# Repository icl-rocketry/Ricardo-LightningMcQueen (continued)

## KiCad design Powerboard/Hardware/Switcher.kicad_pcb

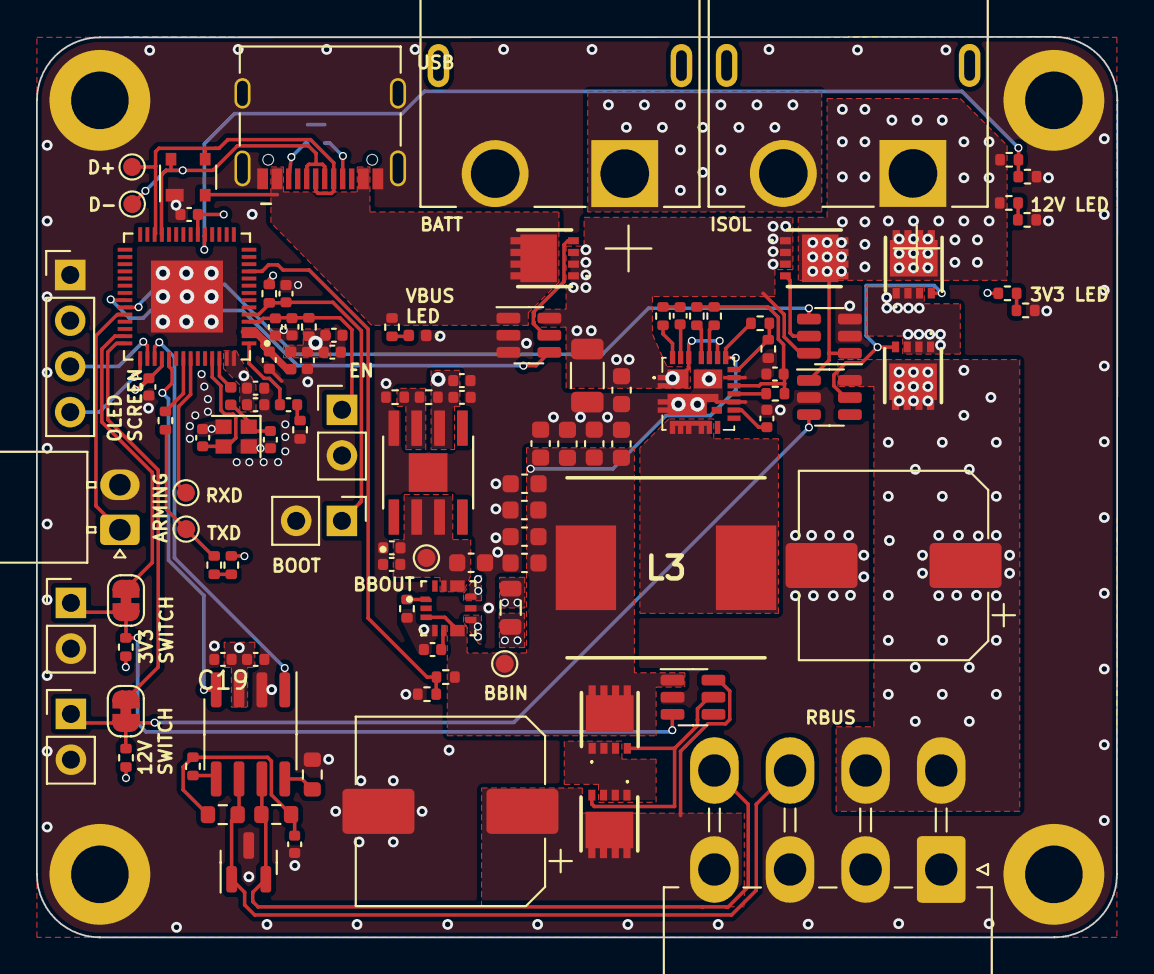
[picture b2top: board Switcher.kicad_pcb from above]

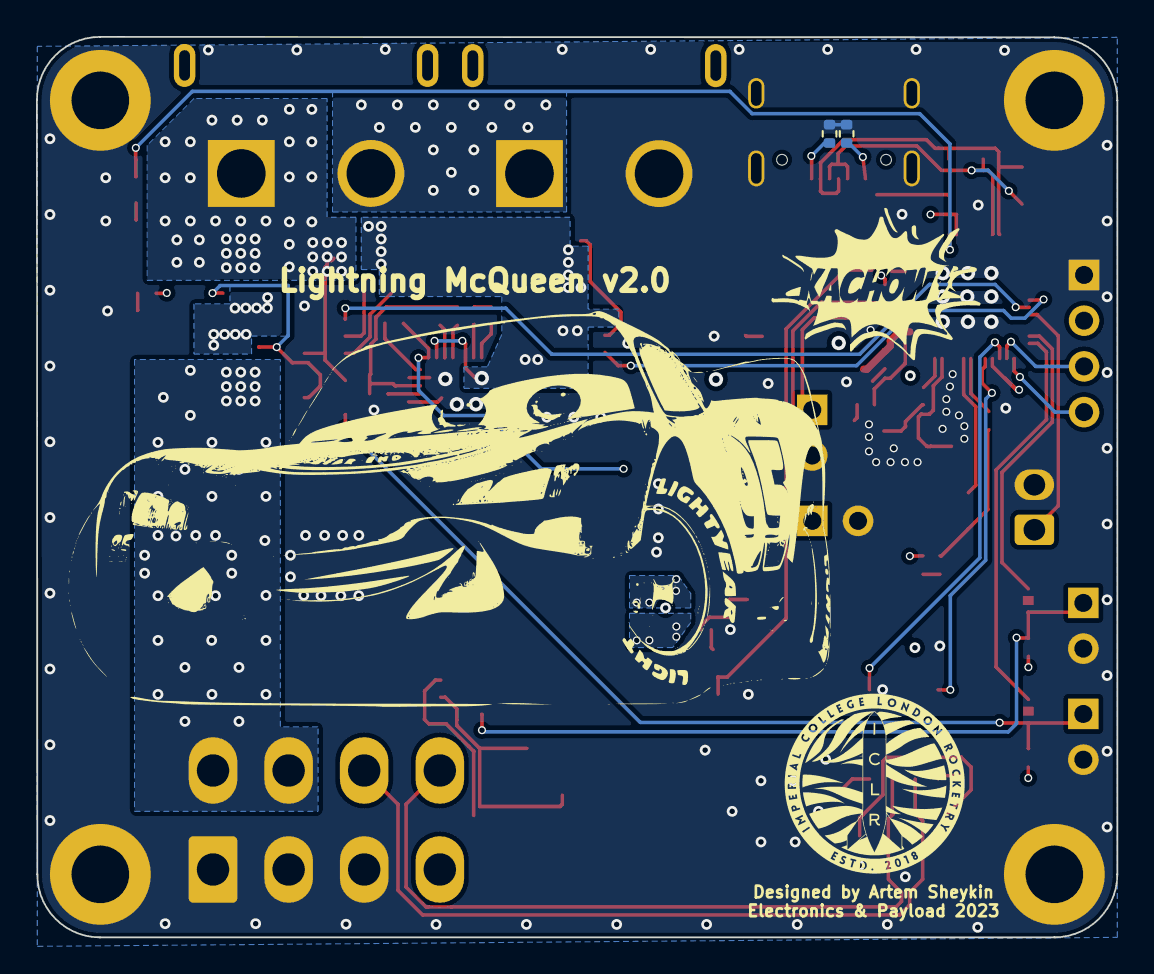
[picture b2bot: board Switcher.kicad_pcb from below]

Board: 4 copper layers, 60.0 x 50.0 mm, 116 parts (3 on the bottom side), 68 nets.

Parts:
3V3LED1: 3V3LED; R_0402_1005Metric
12VLED1: 12V_LED; R_0402_1005Metric
BOOTJUMPER1: Conn_01x02_Male; PinHeader_1x02_P2.54mm_Vertical
C1, C19, C51, C53: 10uF; C_0402_1005Metric
C2, C4, C7, C46, C49: 1uF; C_0402_1005Metric
C3, C5, C6, C8, C10, C11, C42, C54: 0.1uF; C_0402_1005Metric
C9: 10nF; C_0402_1005Metric
C12: DNP; C_0402_1005Metric
C13, C14: C; C_0402_1005Metric
C15, C25, C30, C32, C34, C36, C38, C50: 22uF; C_0603_1608Metric
C17: 10uF; C_0603_1608Metric
C18: 100nF; C_0402_1005Metric
C20: 47nF; C_0402_1005Metric
C23: 1000uF; CP_Elec_10x10
C24: 180uF; CP_Elec_10x10
C40: 47uF; C_1206_3216Metric
C44: 100nF; C_0603_1608Metric
C47, C52: 4.7uF; C_0402_1005Metric
D1: SP0503BAHT; SOT-143
D2: SM712_SOT23; SOT-23
ENJUMPER1: Conn_01x02_Male; PinHeader_1x02_P2.54mm_Vertical
H1, H2, H3, H4: MountingHole_Pad; MountingHole_3.2mm_M3_DIN965_Pad
IC2: SiC437BED-T1-GE3; SiC437BEDT1GE3
J1: Conn_01x03_MountingPin; Molex_Nano-Fit_105313-xx02_1x02_P2.50mm_Horizontal
J3: USB_C_Receptacle_USB2.0; USB_C_Receptacle_Palconn_UTC16-G
J4, J6: Conn_01x02_Male; PinHeader_1x02_P2.54mm_Vertical
J5: Conn_01x08_Male; Molex_Mini-Fit_Jr_5569-08A2_2x04_P4.20mm_Horizontal
J7, J9: XT60PW-M; AMASS_XT60PW-M
J8: Conn_01x04_Male; PinHeader_1x04_P2.54mm_Vertical
JP2, JP3: SolderJumper_2_Bridged; SolderJumper-2_P1.3mm_Bridged_RoundedPad1.0x1.5mm
L1: 2.0nH; L_0402_1005Metric
L2: 20nH; L_0402_1005Metric
L3: SRP1050WA-3R3M; INDPM110100X540N
L5: 1uH; L_0805_2012Metric
Q1, Q2, Q3, Q4, Q5, Q6: PXP012-30QLJ; PXP01230QLJ
R1: 14k; R_0402_1005Metric
R2: 56k; R_0402_1005Metric
R3, R6: 10K; R_0402_1005Metric
R4: 499; R_0402_1005Metric
R5, R7, R12: 470; R_0402_1005Metric
R8: DNP; R_0402_1005Metric
R9: 3k; R_0402_1005Metric
R10, R11: 5.1k; R_0402_1005Metric
R13, R18, R19, R21, R22, R24, R25: 10k; R_0402_1005Metric
R14: 47k; R_0402_1005Metric
R15: 0; R_0603_1608Metric
R16, R17: 60; R_0603_1608Metric
R20: 45k; R_0402_1005Metric
R23: 0; R_0402_1005Metric
R26: 160k; R_0402_1005Metric
R29: 51k; R_0402_1005Metric
R30: 2.2; R_0402_1005Metric
R31: 200k; R_0402_1005Metric
TP1: locked; TestPoint_Pad_D1.0mm
TP2, TP3, TP4, TP5, TP6: TestPoint; TestPoint_Pad_D1.0mm
TXLED1: TX_LED; R_0402_1005Metric
U1, U6, U7, U8: LTC4412xS6; TSOT-23-6
U2: ESP32-S3; QFN40P700X700X90-57N
U4: MAX77827AEFD+T; CONV_MAX77827AEFD+T
U5: SN65HVD230; SOIC-8_3.9x4.9mm_P1.27mm
U10: SC4215; SOIC127P599X175-9N
USBLED1: USB_LED; LED_0402_1005Metric
Y1: 40MHz±10ppm; Crystal_SMD_2016-4Pin_2.0x1.6mm
locked: LOGO; LMQ

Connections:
+3V3: C1.1, C4.1, C5.1, C7.1, C9.1, C10.1, C11.1, C18.1, C19.1, C53.2, C54.2, J8.2, L1.1, R2.1, R3.1, R5.1, R6.1, R7.2, R18.1, R19.1, U2.20 (VDD3P3_RTC), U2.46 (VDD3P3_CPU), U2.55 (VDDA), U2.56 (VDDA), U5.3 (VCC), U10.6 (VOUT)
+12V: J9.1 (+), Q4.5 (D_1), Q4.6 (D_2), Q4.7 (D_3), Q4.8 (D_4), Q4.9 (D_5), Q5.5 (D_1), Q5.6 (D_2), Q5.7 (D_3), Q5.8 (D_4), Q5.9 (D_5), R9.1, R14.1, U1.1 (VIN), U7.1 (VIN)
/3V3Filter/BBOUT: C50.1, C51.1, C52.1, TP6.1, U4.11 (OUT), U4.13 (OUTS), U10.2 (EN), U10.3 (VIN)
/3V3Filter/BIAS: C49.1, U4.5 (BIAS)
/3V3Filter/FBIn: R2.2, R13.1, U10.7 (ADJ)
/3V3Filter/LX1: L5.1, U4.8 (LX1)
/3V3Filter/LX2: L5.2, U4.10 (LX2)
/3V3Filter/SEL: R1.1, U4.1 (SEL)
/3V3LOG: R24.2, R26.1, U2.11 (GPIO6/ADC1_CH5)
/3V3_SWITCH: JP2.2 (B), U2.41 (GPIO36)
/12V_SWITCH: JP3.2 (B), U2.42 (GPIO37)
/BOOT: BOOTJUMPER1.1, C8.1, R6.2, U2.5 (GPIO0/BOOT)
/Bucks/BOOT: C42.1, IC2.23 (BOOT)
/Bucks/FB: IC2.17 (FB), R20.1, R21.1
/Bucks/MODE_1: IC2.21 (_MODE_1), R29.2
/Bucks/MODE_2: IC2.20 (MODE_2), R31.1
/Bucks/PHASE: IC2.24 (PHASE), R30.1
/Bucks/SW: IC2.5 (SW_1), IC2.6 (SW_2), IC2.7 (SW_3), IC2.8 (SW_4), IC2.9 (SW_5), IC2.30 (SW_6), L3.2
/Bucks/Vdd: C46.2, IC2.15 (VDD), R25.1, R29.1, R31.2
/CAN+: D2.2 (A2), J5.8, R16.1, U5.7 (CANH)
/CAN-: D2.1 (A1), J5.7, R17.2, U5.6 (CANL)
/CAN/Vref: R23.1, U5.5 (Vref)
/CAN_RX: U2.47 (MTDI/JTAG/GPIO41), U5.4 (R)
/CAN_TX: U2.45 (MTDO/JTAG/GPIO40), U5.1 (D)
/CHIP_PU: C2.1, C3.1, ENJUMPER1.1, R3.2, U2.4 (CHIP_PU/RESET)
/Data+: D1.3 (K), J3.A7 (D-), J3.B7 (D-), TP1.1, U2.26 (GPIO20/USB_D+/ADC2_CH9)
/Data-: D1.4 (K), J3.A6 (D+), J3.B6 (D+), TP2.1, U2.25 (GPIO19/USB_D-/ADC2_CH8)
/DeploymentVoltage: R14.2, R22.1, U2.19 (GPIO14/ADC2_CH3)
/LIPOPOWER: U1.4 (STAT), U2.37 (SPICLK_P/GPIO47)
/PDU_EN: J1.1, U2.38 (GPIO33)
/SCL: J8.3, U2.44 (MTCK/JTAG/GPIO39)
/SDA: J8.4, U2.43 (GPIO38)
/TXD: R4.1, TP4.1, TXLED1.1 (K)
/USBPOWER: U2.36 (SPICLK_N/GPIO48), U8.4 (STAT)
GND: 3V3LED1.1 (K), 12VLED1.1 (K), BOOTJUMPER1.2, C1.2, C2.2, C3.2, C4.2, C5.2, C6.2, C7.2, C8.2, C9.2, C10.2, C11.2, C13.2, C14.2, C15.1, C17.2, C18.2, C19.2, C20.2, C23.2, C24.2, C25.1, C30.1, C32.1, C34.1, C36.1, C38.1, C40.2, C44.2, C46.1, C47.2, C49.2, C50.2, C51.2, C52.2, C53.1, C54.1, D1.1 (A), D2.3 (common), ENJUMPER1.2, H1.1, H2.1, H3.1, H4.1, IC2.3 (P_GND_1), IC2.4 (P_GND_2), IC2.13 (P_GND_3), IC2.16 (A_GND), IC2.25 (AGND), IC2.27 (PGND), IC2.29 (P_GND_4), J1.2, J3.A1 (GND), J3.A12 (GND), J3.B1 (GND), J3.B12 (GND), J3.S1 (SHIELD), J4.2, J5.1, J5.2, J5.3, J6.2, J7.2 (-), J8.1, R1.2, R8.1, R10.2, R11.1, R13.2, R15.2, R21.2, R22.2, R26.2, U1.2 (GND), U1.3 (CTL), U2.57 (GND), U4.4 (AGND), U4.9 (PGND), U5.2 (GND), U6.2 (GND), U7.2 (GND), U8.2 (GND), U8.3 (CTL), U10.8 (GND), U10.9 (GND), USBLED1.1 (K), Y1.2, Y1.4
unnamed: 3V3LED1.2 (A), R7.1
unnamed: 12VLED1.2 (A), R9.2
unnamed: C6.1, L1.2, U2.2 (VDD3P3), U2.3 (VDD3P3)
unnamed: C12.1, R8.2
unnamed: C14.1, L2.2, Y1.1
unnamed: C20.1, R16.2, R17.1, R23.2
unnamed: C42.2, R30.2
unnamed: C40.1, C44.1, IC2.1 (V_IN_1), IC2.2 (V_IN_2), IC2.19 (EN), IC2.22 (VIN_1), IC2.26 (VIN_2), Q5.1 (S_1), Q5.2 (S_2), Q5.3 (S_3), Q6.1 (S_1), Q6.2 (S_2), Q6.3 (S_3), U1.6 (SENSE), U8.6 (SENSE)
unnamed: IC2.14 (P_GOOD), R25.2
unnamed: C47.1, IC2.12 (V_DRV)
unnamed: J3.A5 (CC1), R10.1
unnamed: J3.B5 (CC2), R11.2
unnamed: J4.1, JP2.1 (A), R18.2, U6.3 (CTL)
unnamed: C23.1, J5.4, Q1.5 (D_1), Q1.6 (D_2), Q1.7 (D_3), Q1.8 (D_4), Q1.9 (D_5), U6.6 (SENSE)
unnamed: C24.1, J5.5, J5.6, Q3.5 (D_1), Q3.6 (D_2), Q3.7 (D_3), Q3.8 (D_4), Q3.9 (D_5), U7.6 (SENSE)
unnamed: J6.1, JP3.1 (A), R19.2, U7.3 (CTL)
unnamed: J7.1 (+), J9.2 (-)
unnamed: Q1.4 (G), Q2.4 (G), U6.5 (GATE)
unnamed: Q1.1 (S_1), Q1.2 (S_2), Q1.3 (S_3), Q2.1 (S_1), Q2.2 (S_2), Q2.3 (S_3)
unnamed: Q3.4 (G), Q4.4 (G), U7.5 (GATE)
unnamed: Q3.1 (S_1), Q3.2 (S_2), Q3.3 (S_3), Q4.1 (S_1), Q4.2 (S_2), Q4.3 (S_3)
unnamed: Q5.4 (G), U1.5 (GATE)
unnamed: Q6.4 (G), U8.5 (GATE)
unnamed: R5.2, TXLED1.2 (A)
unnamed: C12.2, U2.1 (LNA_IN/RF)
unnamed: TP5.1, U2.50 (U0RXD/PROG/GPIO44)
unnamed: R4.2, U2.49 (U0TXD/PROG/GPIO43)
unnamed: C13.1, U2.53 (XTAL_N), Y1.3
unnamed: L2.1, U2.54 (XTAL_P)
unnamed: R15.1, U5.8 (Rs)
unnamed: R12.2, USBLED1.2 (A)
RBUS_uC_V: C15.2, C17.1, C25.2, C30.2, C32.2, C34.2, C36.2, C38.2, IC2.18 (V_OUT), L3.1, Q2.5 (D_1), Q2.6 (D_2), Q2.7 (D_3), Q2.8 (D_4), Q2.9 (D_5), R20.2, R24.1, TP3.1, U4.3 (EN), U4.6 (IN), U6.1 (VIN)
VBUS: D1.2 (K), J3.A4 (VBUS), J3.A9 (VBUS), J3.B4 (VBUS), J3.B9 (VBUS), Q6.5 (D_1), Q6.6 (D_2), Q6.7 (D_3), Q6.8 (D_4), Q6.9 (D_5), R12.1, U8.1 (VIN)

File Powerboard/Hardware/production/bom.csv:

Designator,Footprint,Quantity,Value,LCSC Part #
3V3LED1,0402,1,CYAN_LED,
"BATTLED1, CANRXLED1",0402,2,ORANGE_LED,
"BOOTJUMPER1, ENJUMPER1, J4, J6",PinHeader_1x02_P2.54mm_Vertical,4,Conn_01x02_Male,
"C1, C19, C51, C53",0402,4,10uF,
"C10, C11, C3, C42, C5, C54, C6, C8",0402,8,0.1uF,
"C12, R8",0402,2,DNP,
"C13, C14",0402,2,11pF,
"C15, C25, C30, C32, C34, C36, C38, C50",0603,8,22uF,
C17,0603,1,10uF,
C18,0402,1,100nF,
"C2, C4, C46, C49, C7",0402,5,1uF,
C20,0402,1,47nF,
C23,CP_Elec_10x10,1,1000uF,
C24,CP_Elec_10x10,1,180uF,
C40,1206,1,47uF,
C44,0603,1,100nF,
"C47, C52",0402,2,4.7uF,
C9,0402,1,10nF,
CANTXLED1,0402,1,EMERALD_LED,
D1,SOT-143,1,SP0503BAHT,
D2,SOT-23,1,SM712_SOT23,
DEPLED1,0402,1,RED_LED,
"H1, H2, H3, H4",MountingHole_3.2mm_M3_DIN965_Pad,4,MountingHole_Pad,
IC2,SiC437BEDT1GE3,1,SiC437AED-T1-GE3,
J1,Molex_Nano-Fit_105313-xx02_1x02_P2.50mm_Horizontal,1,Conn_01x03_MountingPin,
J2,PinHeader_1x02_P2.54mm_Vertical,1,FAN,
J3,USB_C_Receptacle_Palconn_UTC16-G,1,USB_C_Receptacle_USB2.0,
J5,Molex_Mini-Fit_Jr_5569-08A2_2x04_P4.20mm_Horizontal,1,Conn_01x08_Male,
"J7, J9",AMASS_XT60PW-M,2,XT60PW-M,
J8,PinHeader_1x04_P2.54mm_Vertical,1,Conn_01x04_Male,
"JP1, JP2",SolderJumper-2_P1.3mm_Bridged_RoundedPad1.0x1.5mm,2,SolderJumper_2_Bridged,
L1,0402,1,2.0nH,
L2,0402,1,20nH,
L3,INDPM110100X540N,1,SRP1050WA-3R3M,
L5,0805,1,1uH,
LOGICLED1,0402,1,BLUE_LED,
Q1,SOT-723,1,"SSM3K15AMFV,L3F",
"Q10, Q7, Q8, Q9",SQS850ENT1_GE3,4,SQS141ELNW-T1_GE3,
"Q5, Q6",PXP01230QLJ,2,PXP012-30QLJ,
R1,0402,1,14k,
"R10, R11, R12",0402,3,5.1k,
"R13, R18, R21, R22, R24, R25, R3, R32, R35, R6",0402,10,10k,
"R14, R28",0402,2,47k,
R15,0603,1,0,
"R16, R17",0603,2,60,
"R19, R34, R36",0402,3,1k,
R2,0402,1,56k,
R20,0402,1,45k,
R23,0402,1,0,
R26,0402,1,160k,
"R27, R9",0402,2,3k,
R29,0402,1,51k,
R30,0402,1,2.2,
R31,0402,1,100k,
"R33, R5, R7",0402,3,470,
R4,0402,1,499,
"TP1, TP2, TP3, TP4, TP5, TP6",TestPoint_Pad_D1.0mm,6,TestPoint,
TXLED1,0402,1,GREEN_LED,
"U1, U6, U7, U8",TSOT-23-6,4,LTC4412xS6,
U10,SOIC127P599X175-9N,1,SC4215,
U2,QFN40P700X700X90-57N,1,ESP32-S3,
U4,CONV_MAX77827AEFD+T,1,MAX77827AEFD+T,
U5,SOIC-8_3.9x4.9mm_P1.27mm,1,SN65HVD230,
USBLED1,0402,1,WHITE_LED,
Y1,Crystal_SMD_2016-4Pin_2.0x1.6mm,1,40MHz±10ppm,

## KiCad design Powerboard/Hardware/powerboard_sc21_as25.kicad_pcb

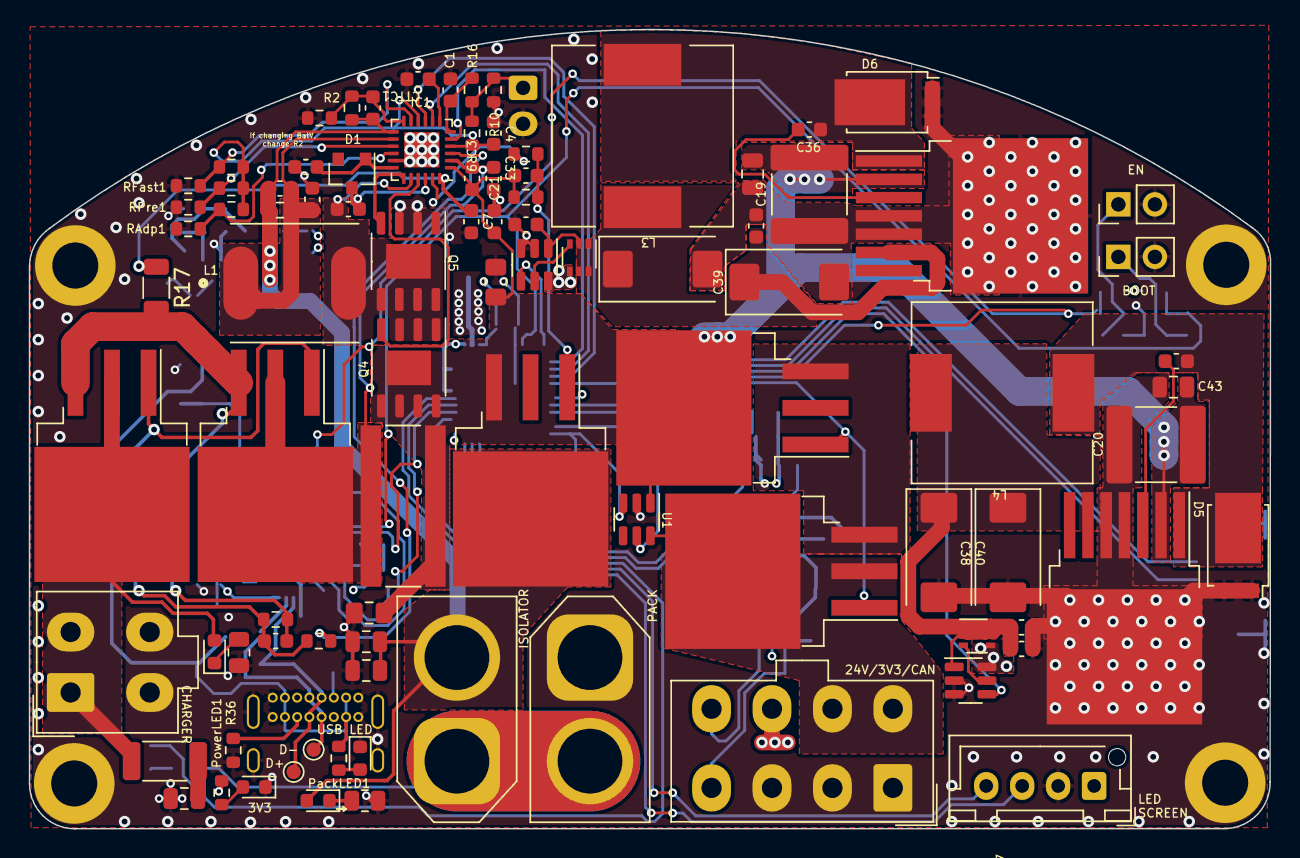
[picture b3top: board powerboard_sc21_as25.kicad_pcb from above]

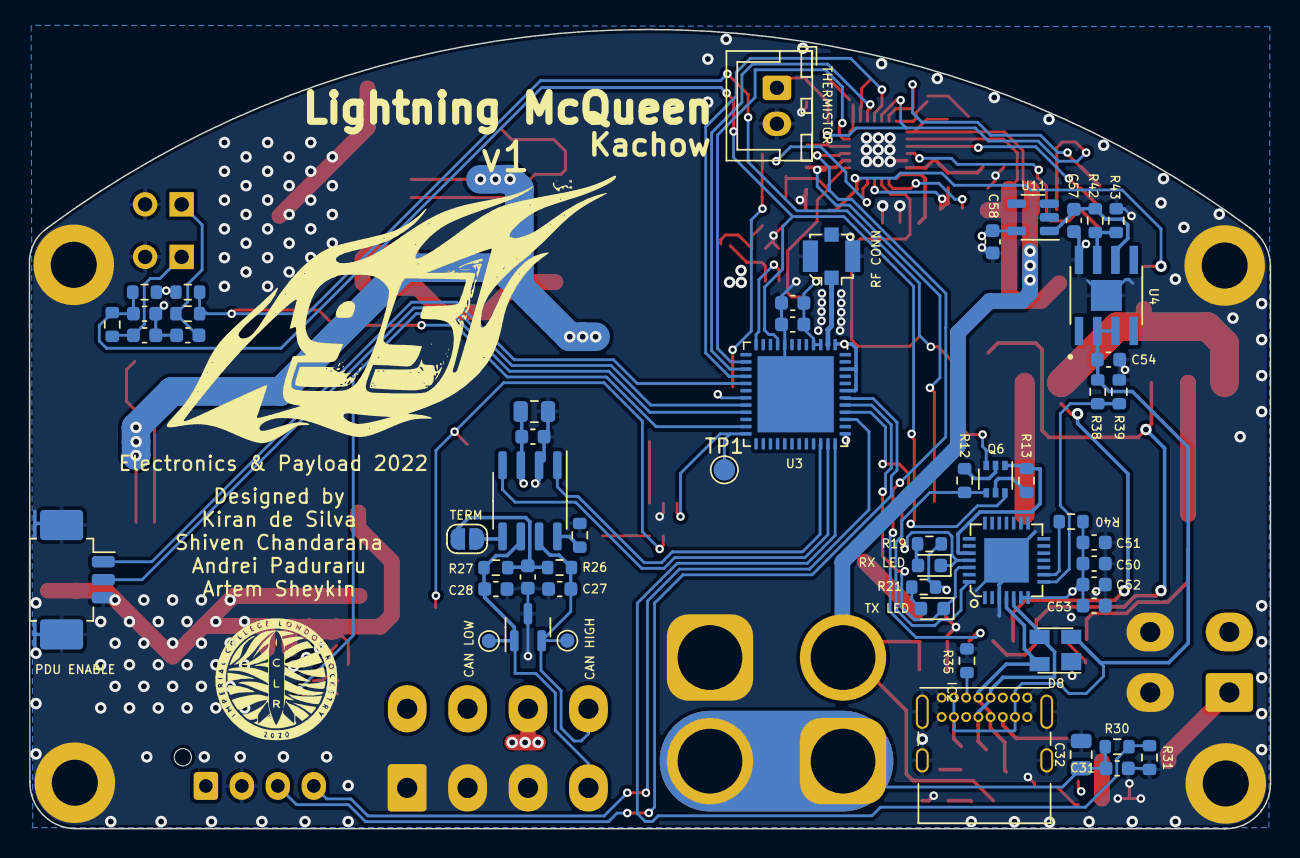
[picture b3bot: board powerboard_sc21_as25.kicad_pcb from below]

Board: 4 copper layers, 86.3 x 55.6 mm, 151 parts (56 on the bottom side), 83 nets.

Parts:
C1, C3, C6, C10, C11, C14, C15, C21, C24, C26, C31, C33, C48, C49, C51, C53: 0.1uF; C_0603_1608Metric
C2, C4, C5, C7, C17, C18: 1uF; C_0603_1608Metric
C8, C9: 10uF; C_0805_2012Metric_Pad1.18x1.45mm_HandSolder
C12, C13, C25, C32: 10uF; C_0805_2012Metric
C16: 2.2uF; C_0805_2012Metric
C19, C20: 47uF; C_2220_5650Metric
C22, C54, C57: 10uF; C_0603_1608Metric
C23: 100nF; C_0603_1608Metric
C27: 220pF; C_0603_1608Metric
C28: 220 pF; C_0603_1608Metric
C36, C37: 0.01uF; C_0603_1608Metric
C38, C39, C40, C41: 330uF; CP_EIA-7343-30_AVX-N
C42, C43: 0.47uF; C_0805_2012Metric
C44, C45: 22uF; C_0603_1608Metric
C50: 1.0uF; C_0603_1608Metric
C52, C58: 4.7uF; C_0603_1608Metric
CTTC1: 22nF; C_0603_1608Metric
Cff1: 22pF; C_0603_1608Metric
D1: BAT54; D_SOT-23_ANK
D2, D3, D7, D9: LED; LED_0603_1608Metric
D4: SM712_SOT23; SOT-23
D5, D6: DST1550S; TO-277B
D8: SP0503BAHT; SOT-143
H1, H2, H3, H4: MountingHole_Pad; MountingHole_3.2mm_M3_DIN965_Pad
IC1: BQ24618RGET-iclr; VQFN-24-1EP_4x4mm_P0.5mm_EP2.45x2.45mm
IC2: CP2102; QFN28G_0.5-5X5MM
J1: Thermistor Connection 103AT NTC; JST_XH_B2B-XH-A_1x02_P2.50mm_Vertical
J2, J3: Conn_01x02_Male; PinHeader_1x02_P2.54mm_Vertical
J4: Conn_01x08_Male; Molex_Mini-Fit_Jr_5566-08A_2x04_P4.20mm_Vertical
J5: Conn_01x04_Male; Molex_Mini-Fit_Jr_5566-04A_2x02_P4.20mm_Vertical
J6: Conn_01x02_Male; AMASS_XT60-M_1x02_P7.20mm_Vertical
J7: IsolationSwitch; AMASS_XT60-M_1x02_P7.20mm_Vertical
J8: USB_C_Receptacle_USB2.0; USB_C_Receptacle_GCT_USB4085
J9: Conn_Coaxial; U.FL_Molex_MCRF_73412-0110_Vertical
J10: Conn_01x04_Male; JST_XH_B4B-XH-AM_1x04_P2.50mm_Vertical
J11: Conn_01x03_MountingPin; Molex_PicoBlade_53261-0371_1x03-1MP_P1.25mm_Horizontal
JP1: SolderJumper_2_Open; SolderJumper-2_P1.3mm_Open_RoundedPad1.0x1.5mm
L1: 6.8uH; INDM8681X400N
L3, L4: 15uH; L_12x12mm_H8mm
PackLED1: LED; LED_0603_1608Metric
PowerLED1: LED; LED_0603_1608Metric
Q1, Q2, Q3, Q7, Q8: RSJ250P10TL; TO-263-3_TabPin2
Q4, Q5: RS1G120MN; HSOP-8-1EP_3.9x4.9mm_P1.27mm_EP2.41x3.1mm
Q6: MMDT2222A; SOT-363_SC-70-6
Q9, Q10: MCH6351; SOT-363_SC-70-6
R1, R4, R11, R12, R13, R24, R31, R43: 10k; R_0603_1608Metric
R2: 110k; R_0603_1608Metric
R3, R5, R7, R14, R15: 100k; R_0603_1608Metric
R6, R8, R19, R21, R22, R37: 470; R_0603_1608Metric
R9: 2.7k; R_0603_1608Metric
R10: 10.5k; R_0603_1608Metric
R16: 100; R_0603_1608Metric
R17: 10; R_1206_3216Metric
R18, R32: 1k; R_0603_1608Metric
R20: 2; R_2010_5025Metric
R26, R27: 60; R_0603_1608Metric
R28, R29: 3k; R_0805_2012Metric
R30: 75k; R_0603_1608Metric
R35, R36: 5.1k; R_0603_1608Metric
R38: 24k; R_0603_1608Metric
R39: 47k; R_0603_1608Metric
R40: 4.7k; R_0603_1608Metric
R42: 56k; R_0603_1608Metric
RAC1: FCSL110R010FER; RESC50110X70N
RAdp1: 150k; R_0603_1608Metric
RFast1: 32k; R_0603_1608Metric
RPre1: 13k; R_0603_1608Metric
RSR1: 10m; R_0603_1608Metric
TP1: TestPoint; TestPoint_Pad_D1.5mm
TP14, TP15, TP23, TP24: TestPoint; TestPoint_Pad_D1.0mm
U1, U8, U9: LTC4412xS6; TSOT-23-6
U2: SN65HVD230; SOIC-8_3.9x4.9mm_P1.27mm
U3: ESP32-PICO-D4; QFN-48-1EP_7x7mm_P0.5mm_EP5.3x5.3mm
U4: SC4216H; SOIC127P599X175-9N
U6, U7: LM2679T-3.3-iclr; TO-263-7_TabPin4
U11: LTC4411; SOT-23-5

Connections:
+3V3: C22.1, C23.1, C24.1, C25.1, C50.1, C51.1, C52.2, C53.2, C58.1, IC2.6 (VDD), IC2.7 (REGIN), J4.7, J10.1, Q9.4 (S), Q10.4 (S), R4.1, R11.1, R19.2, R21.2, R22.2, R40.1, U2.3 (VCC), U3.1 (VDDA), U3.3 (VDDA3P3), U3.4 (VDDA3P3), U3.19 (VDD3P3_RTC), U3.37 (VDD3P3_CPU), U3.43 (VDDA), U3.46 (VDDA), U8.6 (SENSE), U9.6 (SENSE), U11.5 (OUT)
+24V: C3.2, C8.1, C9.1, C15.1, C19.1, C20.1, C21.1, C42.1, C43.1, IC1.1 (ACN), Q3.3, Q4.5 (D), Q4.6 (D), Q4.7 (D), Q4.8 (D), Q4.9 (D), Q8.2, R15.2, RAC1.2, U1.1 (VIN), U6.2 (VIN), U7.2 (VIN)
/3.3STAT1: U3.12 (IO32), U9.4 (STAT)
/3.3STAT2: U3.21 (IO15), U8.4 (STAT)
/BATTSTAT1: IC1.5 (STAT1), U3.14 (IO25)
/BATTSTAT2: IC1.9 (STAT2), U3.16 (IO27)
/BOOT: Q6.3 (C2), R8.2, R11.2, U3.23 (IO0)
/Battery Charger/ACSET: IC1.16 (ACSET), R3.2, RAdp1.1
/Battery Charger/BTST: C6.2, D1.1 (K), IC1.22 (BTST)
/Battery Charger/CE: C4.2, IC1.4 (CE), IC1.10 (VREF), R3.1, R5.1, R7.1, R9.2
/Battery Charger/ICSET2: IC1.15 (ISET2), R5.2, RPre1.1
/Battery Charger/LODRV: IC1.19 (LODRV), Q5.4 (G)
/Battery Charger/PH: C6.1, IC1.20 (PH), L1.2, Q4.1 (S), Q4.2 (S), Q4.3 (S), Q5.5 (D), Q5.6 (D), Q5.7 (D), Q5.8 (D), Q5.9 (D)
/Battery Charger/Q1-G: C14.2, Q1.1, Q2.1, R14.2, R18.1
/Battery Charger/Q1-S: C14.1, Q1.3, Q2.3, R14.1, R17.2
/Battery Charger/Q3-D: C11.2, C12.1, C13.1, Cff1.2, IC1.13 (SRN), J7.2, PackLED1.2 (A), Q3.2, R2.2, RSR1.1
/Battery Charger/Q4-G: IC1.21 (HIDRV), Q4.4 (G)
/Battery Charger/SRP: C10.1, C11.1, IC1.14 (SRP), L1.1, RSR1.2
/Battery Charger/VCC: C7.2, IC1.24 (VCC), R17.1
/Battery Charger/VFB: Cff1.1, IC1.12 (VFB), R1.2, R2.1
/CANH: C27.2, D4.2 (A2), J4.8, R26.1, TP15.1, U2.7 (CANH)
/CANL: C28.2, D4.1 (A1), J4.4, R27.2, TP14.1, U2.6 (CANL)
/CAN_RX: U2.4 (R), U3.35 (IO18)
/CAN_TX: U2.1 (D), U3.34 (IO5)
/CHARGE: R30.2, R31.1, U3.36 (IO23)
/DTR: IC2.28 (DTR), Q6.4 (E2), R12.2
/EN: C2.2, Q6.6 (C1), R4.2, R6.2, U3.9 (EN)
/EXT_LED: J11.1, U3.17 (IO14)
/LNA_IN: J9.1 (In), U3.2 (LNA_IN)
/LPC_24V: TP1.1, U1.3 (CTL), U3.24 (IO4)
/PDU_EN: J11.2, U3.20 (IO13)
/PG: IC1.8 (~PG), U3.15 (IO26)
/RTS: IC2.24 (RTS), Q6.1 (E1), R13.2
/RXD: D2.1 (K), IC2.25 (RXD), U3.40 (U0RXD/IO3)
/SCL: J10.4, U3.39 (IO22)
/SDA: J10.3, U3.42 (IO21)
/TXD: D3.1 (K), IC2.26 (TXD), U3.41 (U0TXD/IO1)
/USB To UART/D+: D8.4 (K), IC2.4 (D+), J8.A6 (D+), J8.B6 (D+), TP24.1
/USB To UART/D-: D8.3 (K), IC2.5 (D-), J8.A7 (D-), J8.B7 (D-), TP23.1
/Vref: JP1.1 (A), U2.5 (Vref)
GND: C1.2, C2.1, C4.1, C5.2, C7.1, C8.2, C9.2, C10.2, C12.2, C13.2, C16.2, C17.1, C18.1, C19.2, C20.2, C21.2, C22.2, C23.2, C24.2, C25.2, C26.2, C27.1, C28.1, C31.2, C32.2, C33.1, C38.2, C39.2, C40.2, C41.2, C42.2, C43.2, C44.2, C45.2, C48.2, C49.2, C50.2, C51.2, C52.1, C53.1, C54.1, C57.1, C58.2, CTTC1.1, D4.3 (common), D5.1 (A), D5.2 (A), D6.1 (A), D6.2 (A), D7.1 (K), D8.1 (A), D9.1 (K), H1.1, H2.1, H3.1, H4.1, IC1.17 (GND), IC1.25 (EP), IC2.3 (GND), IC2.29 (EPAD), J1.2, J2.2, J3.2, J4.1, J4.2, J4.3, J5.3, J5.4, J6.1, J8.A1 (GND), J8.A12 (GND), J8.B1 (GND), J8.B12 (GND), J8.S1 (SHIELD), J9.2 (Ext), J10.2, J11.3, J11.MP (MountPin), Q5.1 (S), Q5.2 (S), Q5.3 (S), R1.1, R10.1, R24.2, R28.2, R29.2, R31.2, R35.1, R36.1, R39.1, R43.2, RAdp1.2, RFast1.2, RPre1.2, U1.2 (GND), U2.2 (GND), U3.8 (SENSOR_VN), U3.49 (GND), U4.8 (GND), U4.9 (GND), U6.4 (GND), U6.5 (CURRENT_ADJ), U7.4 (GND), U7.5 (CURRENT_ADJ), U8.2 (GND), U8.3 (CTL), U9.2 (GND), U9.3 (CTL), U11.2 (GND), U11.3 (CTL)
unnamed: C1.1, IC1.6 (TS), R16.1
unnamed: C3.1, C33.2, IC1.2 (ACP), Q2.2, RAC1.1
unnamed: C5.1, D1.2 (A), IC1.18 (REGN)
unnamed: C15.2, Q3.1, R15.1, R32.2
unnamed: C16.1, R20.1
unnamed: C17.2, J2.1, R6.1
unnamed: C18.2, J3.1, R8.1
unnamed: C26.1, JP1.2 (B), R26.2, R27.1
unnamed: C31.1, C32.1, J6.2, J7.1, R30.1
unnamed: C36.1, U6.3 (BOOST)
unnamed: C36.2, D6.3 (K), L3.1, U6.1 (SW)
unnamed: C37.1, U7.3 (BOOST)
unnamed: C37.2, D5.3 (K), L4.1, U7.1 (SW)
unnamed: C38.1, C40.1, C44.1, C48.1, L4.2, Q10.1 (D), Q10.2 (D), Q10.5 (D), Q10.6 (D), U7.6 (FB), U8.1 (VIN)
unnamed: C39.1, C41.1, C45.1, C49.1, L3.2, Q9.1 (D), Q9.2 (D), Q9.5 (D), Q9.6 (D), U6.6 (FB), U9.1 (VIN)
unnamed: C57.2, R42.1, U4.6 (VOUT), U11.1 (IN)
unnamed: CTTC1.2, IC1.7 (TTC)
unnamed: D2.2 (A), R19.1
unnamed: D3.2 (A), R21.1
unnamed: D7.2 (A), R37.2
unnamed: D9.2 (A), R22.1
unnamed: IC1.3 (~ACDRV), R18.2
unnamed: IC1.11 (ISET1), R7.2, RFast1.1
unnamed: IC1.23 (~BATDRV), R32.1
unnamed: IC2.8 (VBUS), R38.2, R39.2
unnamed: IC2.9 (~RST), R40.2
unnamed: J1.1, R9.1, R10.2, R16.2
unnamed: J4.5, J4.6, Q7.2, U1.6 (SENSE)
unnamed: J5.1, J5.2, PowerLED1.2 (A), Q1.2, R20.2
unnamed: J8.A5 (CC1), R35.2
unnamed: J8.B5 (CC2), R36.2
unnamed: PackLED1.1 (K), R28.1
unnamed: PowerLED1.1 (K), R29.1
unnamed: Q6.2 (B1), R12.1
unnamed: Q6.5 (B2), R13.1
unnamed: Q7.1, Q8.1, U1.5 (GATE)
unnamed: Q7.3, Q8.3
unnamed: Q9.3 (G), U9.5 (GATE)
unnamed: Q10.3 (G), U8.5 (GATE)
unnamed: R24.1, U2.8 (Rs)
unnamed: R42.2, R43.1, U4.7 (ADJ)
VBUS: C54.2, D8.2 (K), J8.A4 (VBUS), J8.A9 (VBUS), J8.B4 (VBUS), J8.B9 (VBUS), R37.1, R38.1, U4.2 (EN), U4.3 (VIN)

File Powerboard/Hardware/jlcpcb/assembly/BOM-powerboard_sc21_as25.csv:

Comment,Designator,Footprint,LCSC
470,R22,R_0603_1608Metric,
0.01uF,C37,C_0603_1608Metric,
15uH,L3,L_12x12mm_H8mm,
LED,PackLED1,LED_0603_1608Metric,
22nF,CTTC1,C_0603_1608Metric,
BQ24618RGET-iclr,IC1,VQFN-24-1EP_4x4mm_P0.5mm_EP2.45x2.45mm,
22uF,C44,C_0603_1608Metric,
Conn_01x02_Male,J6,AMASS_XT60-M_1x02_P7.20mm_Vertical,
1uF,C5,C_0603_1608Metric,
0.47uF,C43,C_0805_2012Metric,
RS1G120MN,Q4,HSOP-8-1EP_3.9x4.9mm_P1.27mm_EP2.41x3.1mm,
110k,R2,R_0603_1608Metric,
RSJ250P10TL,Q3,TO-263-3_TabPin2,
0.1uF,C33,C_0603_1608Metric,
32k,RFast1,R_0603_1608Metric,
1uF,C7,C_0603_1608Metric,
FCSL110R010FER,RAC1,RESC50110X70N,
0.1uF,C6,C_0603_1608Metric,
3k,R29,R_0805_2012Metric,
Conn_01x04_Male,J5,Molex_Mini-Fit_Jr_5566-04A_2x02_P4.20mm_Vertical,
330uF,C41,CP_EIA-7343-30_AVX-N,
0.47uF,C42,C_0805_2012Metric,
Conn_01x08_Male,J4,Molex_Mini-Fit_Jr_5566-08A_2x04_P4.20mm_Vertical,
TestPoint,TP23,TestPoint_Pad_D1.0mm,
DST1550S,D5,TO-277B,
0.1uF,C21,C_0603_1608Metric,
1uF,C4,C_0603_1608Metric,
0.1uF,C3,C_0603_1608Metric,
10m,RSR1,R_0603_1608Metric,
MountingHole_Pad,H3,MountingHole_3.2mm_M3_DIN965_Pad,
MCH6351,Q10,SOT-363_SC-70-6,
100k,R5,R_0603_1608Metric,
0.1uF,C10,C_0603_1608Metric,
MountingHole_Pad,H4,MountingHole_3.2mm_M3_DIN965_Pad,
0.1uF,C48,C_0603_1608Metric,
330uF,C40,CP_EIA-7343-30_AVX-N,
Conn_01x02_Male,J2,PinHeader_1x02_P2.54mm_Vertical,
1k,R32,R_0603_1608Metric,
47uF,C20,C_2220_5650Metric,
0.1uF,C11,C_0603_1608Metric,
470,R37,R_0603_1608Metric,
MCH6351,Q9,SOT-363_SC-70-6,
Conn_01x04_Male,J10,JST_XH_B4B-XH-AM_1x04_P2.50mm_Vertical,
LED,D9,LED_0603_1608Metric,
47uF,C19,C_2220_5650Metric,
MountingHole_Pad,H2,MountingHole_3.2mm_M3_DIN965_Pad,
0.1uF,C14,C_0603_1608Metric,
2.2uF,C16,C_0805_2012Metric,
100k,R3,R_0603_1608Metric,
330uF,C39,CP_EIA-7343-30_AVX-N,
150k,RAdp1,R_0603_1608Metric,
LED,PowerLED1,LED_0603_1608Metric,
10.5k,R10,R_0603_1608Metric,
10uF,C12,C_0805_2012Metric,
10,R17,R_1206_3216Metric,
100k,R15,R_0603_1608Metric,
LED,D7,LED_0603_1608Metric,
10uF,C9,C_0805_2012Metric_Pad1.18x1.45mm_HandSolder,
100k,R7,R_0603_1608Metric,
10uF,C8,C_0805_2012Metric_Pad1.18x1.45mm_HandSolder,
10k,R1,R_0603_1608Metric,
LM2679T-3.3-iclr,U6,TO-263-7_TabPin4,
0.1uF,C49,C_0603_1608Metric,
2,R20,R_2010_5025Metric,
22uF,C45,C_0603_1608Metric,
100k,R14,R_0603_1608Metric,
Conn_01x02_Male,J3,PinHeader_1x02_P2.54mm_Vertical,
0.1uF,C1,C_0603_1608Metric,
DST1550S,D6,TO-277B,
5.1k,R36,R_0603_1608Metric,
LM2679T-3.3-iclr,U7,TO-263-7_TabPin4,
LTC4412xS6,U8,TSOT-23-6,
MountingHole_Pad,H1,MountingHole_3.2mm_M3_DIN965_Pad,
0.01uF,C36,C_0603_1608Metric,
TestPoint,TP24,TestPoint_Pad_D1.0mm,
6.8uH,L1,INDM8681X400N,
IsolationSwitch,J7,AMASS_XT60-M_1x02_P7.20mm_Vertical,
1k,R18,R_0603_1608Metric,
3k,R28,R_0805_2012Metric,
RSJ250P10TL,Q8,TO-263-3_TabPin2,
RS1G120MN,Q5,HSOP-8-1EP_3.9x4.9mm_P1.27mm_EP2.41x3.1mm,
100,R16,R_0603_1608Metric,
10uF,C13,C_0805_2012Metric,
RSJ250P10TL,Q2,TO-263-3_TabPin2,
RSJ250P10TL,Q7,TO-263-3_TabPin2,
0.1uF,C15,C_0603_1608Metric,
RSJ250P10TL,Q1,TO-263-3_TabPin2,
330uF,C38,CP_EIA-7343-30_AVX-N,
BAT54,D1,D_SOT-23_ANK,
LTC4412xS6,U9,TSOT-23-6,
LTC4412xS6,U1,TSOT-23-6,
13k,RPre1,R_0603_1608Metric,
2.7k,R9,R_0603_1608Metric,
15uH,L4,L_12x12mm_H8mm,
22pF,Cff1,C_0603_1608Metric,
SN65HVD230,U2,SOIC-8_3.9x4.9mm_P1.27mm,
10uF,C57,C_0603_1608Metric,
4.7k,R40,R_0603_1608Metric,
1uF,C18,C_0603_1608Metric,
4.7uF,C52,C_0603_1608Metric,
220 pF,C28,C_0603_1608Metric,
0.1uF,C24,C_0603_1608Metric,
0.1uF,C51,C_0603_1608Metric,
24k,R38,R_0603_1608Metric,
TestPoint,TP14,TestPoint_Pad_D1.0mm,
0.1uF,C31,C_0603_1608Metric,
470,R21,R_0603_1608Metric,
470,R8,R_0603_1608Metric,
Conn_Coaxial,J9,U.FL_Molex_MCRF_73412-0110_Vertical,
10uF,C22,C_0603_1608Metric,
10k,R13,R_0603_1608Metric,
SM712_SOT23,D4,SOT-23,
Thermistor Connection 103AT NTC,J1,JST_XH_B2B-XH-A_1x02_P2.50mm_Vertical,
MMDT2222A,Q6,SOT-363_SC-70-6,
10k,R43,R_0603_1608Metric,
10uF,C32,C_0805_2012Metric,
4.7uF,C58,C_0603_1608Metric,
10uF,C54,C_0603_1608Metric,
75k,R30,R_0603_1608Metric,
0.1uF,C26,C_0603_1608Metric,
60,R26,R_0603_1608Metric,
ESP32-PICO-D4,U3,QFN-48-1EP_7x7mm_P0.5mm_EP5.3x5.3mm,
220pF,C27,C_0603_1608Metric,
10k,R12,R_0603_1608Metric,
LED,D3,LED_0603_1608Metric,
470,R6,R_0603_1608Metric,
10k,R24,R_0603_1608Metric,
LED,D2,LED_0603_1608Metric,
1uF,C17,C_0603_1608Metric,
Conn_01x03_MountingPin,J11,Molex_PicoBlade_53261-0371_1x03-1MP_P1.25mm_Horizontal,
10uF,C25,C_0805_2012Metric,
10k,R11,R_0603_1608Metric,
SP0503BAHT,D8,SOT-143,
SolderJumper_2_Open,JP1,SolderJumper-2_P1.3mm_Open_RoundedPad1.0x1.5mm,
1.0uF,C50,C_0603_1608Metric,
10k,R31,R_0603_1608Metric,
LTC4411,U11,SOT-23-5,
5.1k,R35,R_0603_1608Metric,
TestPoint,TP15,TestPoint_Pad_D1.0mm,
CP2102,IC2,QFN28G_0.5-5X5MM,
47k,R39,R_0603_1608Metric,
100nF,C23,C_0603_1608Metric,
USB_C_Receptacle_USB2.0,J8,USB_C_Receptacle_GCT_USB4085,
470,R19,R_0603_1608Metric,
1uF,C2,C_0603_1608Metric,
SC4216H,U4,SOIC127P599X175-9N,
10k,R4,R_0603_1608Metric,
0.1uF,C53,C_0603_1608Metric,
56k,R42,R_0603_1608Metric,
60,R27,R_0603_1608Metric,
TestPoint,TP1,TestPoint_Pad_D1.5mm,

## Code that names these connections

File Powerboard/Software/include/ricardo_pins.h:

/*
**********************
* PINS               *
**********************
 */
#pragma once

// static constexpr int BaroCs = 2;
// static constexpr int LoraReset = 4;
// static constexpr int LoraCs = 5;
// static constexpr int LoraInt = 6;

// static constexpr int _SDA = 9;
// static constexpr int _SCL = 32;

// static constexpr int PDU_EN = 26;    //should be 9

// static constexpr int TxCan = 18;
// static constexpr int RxCan = 5;

// static constexpr int BattStat1 = 14;    //should be 14
// static constexpr int BattStat2 = 27;    //should be 27

// static constexpr int Stat1_3V3 = 32;
// static constexpr int Stat2_3V3 = 25;

// static constexpr int LPC_24V = 4;  //should be 4

// static constexpr int Charge = 23;

// static constexpr int PG = 10;   //should be 26


// /*
// **********************
// * PINS               *
// **********************
//  */
// #pragma once

static constexpr int BaroCs = 2;
static constexpr int LoraReset = 4;
static constexpr int LoraCs = 5;
static constexpr int LoraInt = 6;

static constexpr int _SDA = 21;
static constexpr int _SCL = 22;

static constexpr int PDU_EN = 13;

static constexpr int TxCan = 5;
static constexpr int RxCan = 18;

static constexpr int BattStat1 = 25;
static constexpr int BattStat2 = 27;

static constexpr int Stat1_3V3 = 32;
static constexpr int Stat2_3V3 = 25;

static constexpr int LPC_24V = 33;

static constexpr int Charge = 14;

static constexpr int PG = 26;

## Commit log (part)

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2021-12-04 Initial rev of e-match board (adapted from sensorboard schematic)
    Replaced all the ADCs with 4 e-match circuits
2021-12-04 Revert "Jiawei yao 2022 patch 1"
2022-01-29 Added work so far
2022-01-29 Updates changes 29/01/2022
2022-02-01 01022022
2022-02-08 05/02/2022
2022-02-08 08/02/2022 start
2022-02-08 08/02/2022 update
2022-02-08 08/02/2022
    3.3v regulators complete
2022-02-08 08/02/2022 update3
2022-02-08 reverse polarity protection
2022-02-13 13/02/2022
    reverse polarity protection added, some test points, general clear up
2022-02-13 13/02/2022
2022-02-15 update 15/02/2022
2022-02-19 added lpc/24 enable
2022-02-19 19/02/2022
2022-02-22 kicad6 file
2022-02-22 Tidy up Kicad 6
2022-02-26 usb --> uart connection added
2022-02-26 Sorted Labels
2022-02-26 added vbus to 3.3v converter
2022-03-01 Checked the values for battery monitor
2022-03-05 Added thermistor resistor for specific thermistor
2022-03-05 backup file
2022-03-08 isolation switch added
2022-03-25 removed battery monitor
2022-05-24 Added connectors and potential divider for charge measurement
2022-05-24 Swapped remaining p mosfets
2022-06-04 removed charger reverse polarity protection
2022-06-04 changed old mosfets, broke out I2C
2022-06-10 3v3 reg cap & inductor changes, added boost capacitor
2022-06-10 assigned FPs for ceramic caps & most resistors
2022-06-14 added components spreadsheet, changed some caps to ceramic
2022-06-14 actually changed caps this time
2022-06-18 All capacitors selected, most other footprints assigned
2022-06-18 Finished footprint assignment
2022-06-18 changed some FP assignments and imported components
2022-06-21 grouped components by circuit, done CAN transceiver layout.
2022-06-27 Tuesday's changes (I don't remember what I did)
2022-06-28 Finalised buck capacitors, some inital layout
2022-06-28 moving around charger components
2022-07-03 layout
2022-07-04 changed isolation switch position
2022-07-04 started routing, mess at the moment
2022-07-04 removed autosaved
2022-07-06 change some passive values and slight FP changes after orderlist
    some resistor values were really unconventional and some cap footprints had gone out of stock so had to change them.
2022-07-06 forgot to stage the footprint info file
2022-07-06 layout progress
2022-07-07 Fixed USB data pins
2022-07-07 Changed some values and footprints since some went out of stock
2022-07-08 Change RSR and RAC sense resistor to ones rated for 5W
2022-07-08 changed RSR again
2022-07-08 update 2
2022-07-08 changed RSR traces to same layer
    going to check charger layout recommendations again
2022-07-10 Andrei's review, no via fencing on ufl conn
2022-07-11 corrected based on bq24618 guidelines as much as possible
2022-07-14 Removed CAN resistors
2022-07-17 Added connector for PDU EN pin and external LED + routing changes
2022-07-19 silkscreen tidying
2022-07-20 Create firmware
2022-07-23 swapping mosfets the right way around
2022-07-23 super small adjustment
2022-07-26 test
2022-07-27 dan's review
2022-07-28 written some software
2022-07-28 Fixed pin assignments
2022-07-29 Fixed file location and changed a trace width
2022-07-29 Added PCB name on back silkscreen + version numbering
2022-07-29 did some final fixes with track width
2022-07-29 changed can h and i2c lines so vias are more conssitent
2022-07-29 made can h and can l lines closer in length
2022-07-29 battery cmds
2022-07-29 Auto stash before merge of "power-board" and "origin/power-board"
2022-07-30 Added Battery Commands
2022-08-01 re-layed out pdu to improve buck smps stability
2022-08-01 fixes
2022-08-01 Added 3v3 LED, changed LED labels on silkscreen, added Kachow
2022-08-01 software update
2022-08-03 Changed input filter resistors and changed layout to match
2022-08-11 did some stuff
2022-08-11 added comments
2022-08-11 comments
2022-08-13 Fix error in display library
    Due to the use of typeof(). Add build flag to replace it with C++ equivalent
2022-08-16 not much
2022-08-17 not much again
2022-08-25 updated pins and new layout
2022-08-30 pdu enable fix
2022-09-04 battVoltage reading pin changed to 14
2022-09-10 oled still not working
2022-09-12 battvoltage, pdu_en working
2022-09-14 fixed
2022-10-12 removed librnp from submodules
2022-10-12 readded librnp to submodules
2022-11-19 new board
2023-02-04 latest
2023-02-07 added power rail logging
2023-02-25 waiting for review
2023-03-04 changed nanofits for pin headers, made space for usb casing
2023-03-04 fixed board setup
2023-03-09 i2c breakout, general clean up
2023-03-28 vias fixed, ready for review
2023-04-09 kiran/andrei review
2023-04-09 rxd/txd testpoints
2023-04-11 reviewed
2023-05-18 mosfet flipping
2023-05-20 removed 100nf cap, pgood pull up
2023-05-28 3v3logging moved to buck output
2023-06-04 dumbass
2023-06-04 vias under limit, added via to gnda on bb
2023-06-30 nothing
2023-07-01 usbpwr via intersect fix
2023-07-02 new layout
2023-07-02 silkscreen
2023-07-02 fixed cap in wrong place
2023-07-05 new inductor, logging traces rerouted
2023-07-13 order changes + gerbs
2023-07-15 Removed submodule Powerboard/Software/lib/librnp
2023-07-15 had to delete all the stuff in the software folder, dont know wahts going on
2023-07-15 Ricardo-OS-Tempalte copied into software folder without components
2023-07-15 init submodules
2023-07-16 deleted submodules
2023-07-17 deleted everything
2023-07-17 copy of ricardo-os-template
2023-07-17 submodules initialised
2023-07-17 removed extra folders
2023-08-08 state transitions
2023-08-08 Removed submodule Powerboard/Software/components/arduino-esp32
2023-08-08 gitmodules file changed
2023-08-08 gitmodule file changed again
2023-08-08 updated submodules
2023-08-09 added some commands, hardware fixes
2023-08-13 firmware updates
2023-08-14 v2.1
2023-08-16 firmware for v2.0 done
2023-08-19 hardware update
2023-08-22 data lines fix
2023-08-28 added nimbus logo to oled
2023-09-03 can hardware fix, firmware updates
2023-09-05 v2.1 ordering
2023-09-05 3D stuff
2023-09-07 added RC snubber
2023-09-20 some firmware updates
2023-09-28 v2.0 firmware
2023-09-28 pulled latest librrc
2023-09-29 libriccore librnp update
2023-10-07 riccore update, slowed down oled
2023-11-06 submodule changes
2024-06-10 v2.2 hardware
2024-07-20 commit before trying to squish the layout
2024-07-25 shiven layout change
2024-07-29 added rc on gates, post kiran review
2024-07-30 fixed resistor value
2024-07-30 updated mpn on some caps
2024-08-05 changes post 3rd review
2024-08-13 esp32 adc cap was in wrong place
2024-08-16 post Andrei review
2024-08-18 moved efuse upstream of ltc
2024-08-19 final review
2024-08-19 Ordering
2024-08-21 repo cleanup
2024-08-21 changed arduino branch
2024-09-27 fixed dep rail logic being backwards, battV in packet not being updated, and added a fix for the i2c oled causing lag
2025-08-14 Fixed submodules for last v3 commit
2025-08-15 Updated to newest idf version
2025-08-15 correctly updated adc params for >idf5.0
2025-08-16 Pluto edition potential divider
2026-01-27 v4 submodules
2026-01-27 removed build dir
2026-03-12 Initial changes : removed efuse in place of a current sensor and hardware fuse xt60
2026-03-25 feat: Some review updates
2026-03-25 feat: More board review
2026-03-27 feat: Via and track sizes for eurocircuits
2026-04-02 feat: GND and 3V3 plane solid + current sense GND exclusion
2026-04-02 feat: Via size for eurocircuits, adjusted inner layer USBC
    fixing stuff for eurocircuits
2026-05-12 feat: R28
2026-06-24 feat: Changed mosfet to non deprecated version
    Higher input voltage too: SI7135DP-T1-GE3
2026-06-24 cleaned up schematic and bom
2026-06-24 continued
